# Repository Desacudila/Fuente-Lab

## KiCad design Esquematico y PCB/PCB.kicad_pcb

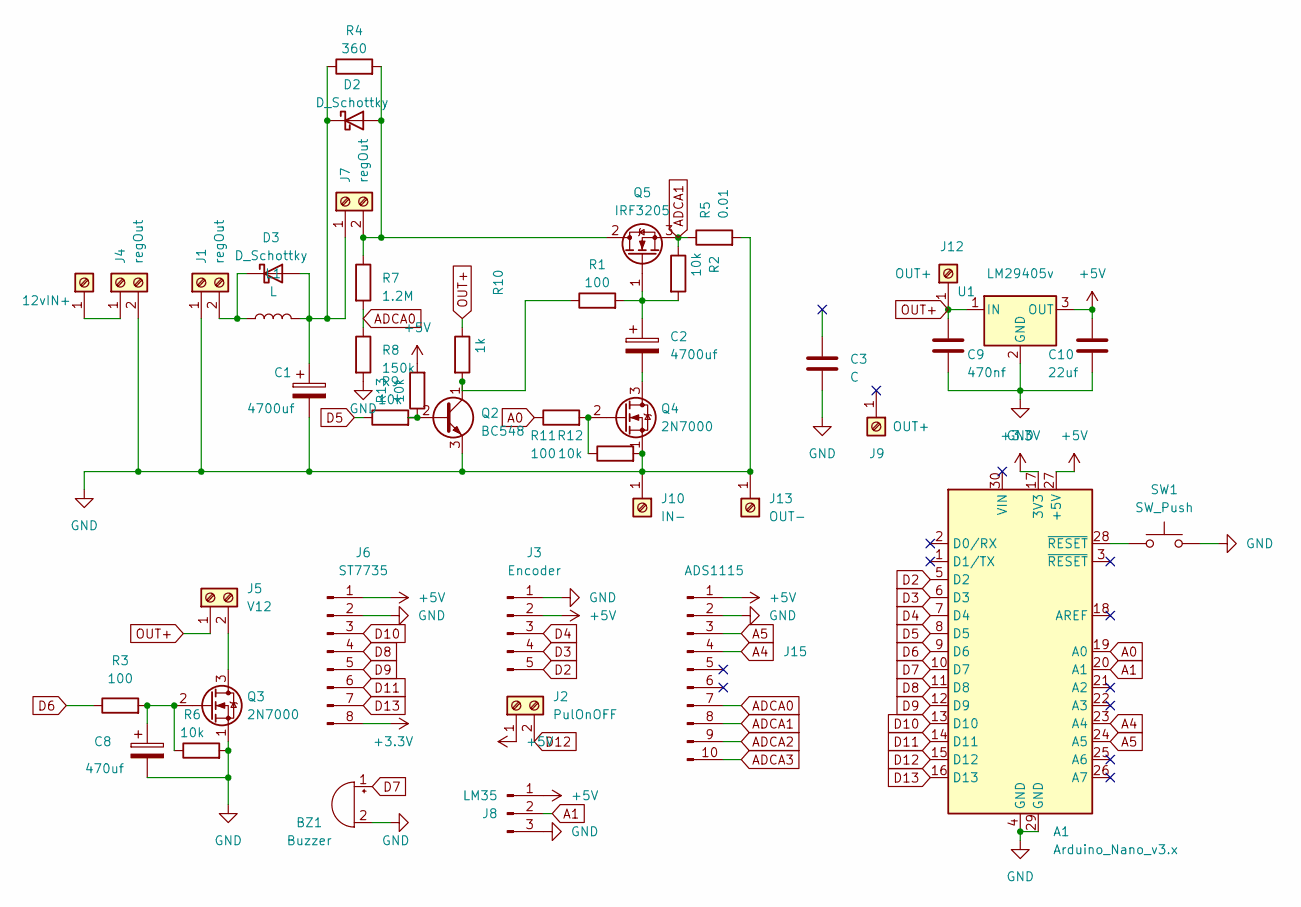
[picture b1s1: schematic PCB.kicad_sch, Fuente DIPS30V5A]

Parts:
A1: Arduino_Nano_v3.x; Arduino_Nano_WithMountingHoles
BZ1: Buzzer; MagneticBuzzer_ProSignal_ABI-010-RC
C1, C2: 4700uf; CP_Radial_D22.0mm_P10.00mm_SnapIn
C3: C; C_Rect_L26.5mm_W7.0mm_P22.50mm_MKS4
C8: 470uf; C_Radial_D10.0mm_H16.0mm_P5.00mm
C9: 470nf; C_Disc_D5.0mm_W2.5mm_P5.00mm
C10: 22uf; CP_Radial_D4.0mm_P2.00mm
D2, D3: D_Schottky; D_DO-201AD_P15.24mm_Horizontal
J1, J4, J7: regOut; Molex_KK-254_AE-6410-02A_1x02_P2.54mm_Vertical
J2: PulOnOFF; Molex_KK-254_AE-6410-02A_1x02_P2.54mm_Vertical
J3: Encoder; Molex_KK-254_AE-6410-05A_1x05_P2.54mm_Vertical
J5: V12; Molex_KK-254_AE-6410-02A_1x02_P2.54mm_Vertical
J6: ST7735; Molex_KK-254_AE-6410-08A_1x08_P2.54mm_Vertical
J8: LM35; Molex_KK-254_AE-6410-03A_1x03_P2.54mm_Vertical
J9, J12: OUT+; Pin_D1.0mm_L10.0mm
J10: IN-; Pin_D1.0mm_L10.0mm
J13: OUT-; Pin_D1.0mm_L10.0mm
J15: ADS1115; PinHeader_1x10_P2.54mm_Vertical
J16: 12vIN+; Pin_D1.0mm_L10.0mm
L1: L; L_Toroid_Vertical_L21.6mm_W8.4mm_P8.38mm_Pulse_G
Q2: BC548; TO-92_Inline
Q3, Q4: 2N7000; TO-92_Inline
Q5: IRF3205; TO-220-3_Vertical
R1, R3, R11: 100; R_Axial_DIN0207_L6.3mm_D2.5mm_P10.16mm_Horizontal
R2, R6, R9, R12, R13: 10k; R_Axial_DIN0207_L6.3mm_D2.5mm_P10.16mm_Horizontal
R4: 360; R_Axial_Power_L38.0mm_W6.4mm_P45.72mm
R5: 0.01; R_2512_6332Metric_Pad1.40x3.35mm_HandSolder
R7: 1.2M; R_Axial_DIN0207_L6.3mm_D2.5mm_P10.16mm_Horizontal
R8: 150k; R_Axial_DIN0207_L6.3mm_D2.5mm_P10.16mm_Horizontal
R10: 1k; R_Axial_DIN0207_L6.3mm_D2.5mm_P10.16mm_Horizontal
SW1: SW_Push; Molex_KK-254_AE-6410-02A_1x02_P2.54mm_Vertical
U1: LM29405v; TO-220-3_Horizontal_TabDown

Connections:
+3.3V: A1.17 (3V3), J6.8
+5V: A1.27 (+5V), C10.1, J2.1, J3.2, J6.1, J8.1, J15.1, R13.2, U1.3 (OUT)
A0: A1.19 (A0), R11.1
A1: A1.20 (A1), J8.2
A4: A1.23 (A4), J15.4
A5: A1.24 (A5), J15.3
ADCA0: J15.7, R7.2, R8.1
ADCA1: J15.8, Q5.3 (S), R2.1, R5.1
ADCA2: J15.9
ADCA3: J15.10
D2: A1.5 (D2), J3.5
D3: A1.6 (D3), J3.4
D4: A1.7 (D4), J3.3
D5: A1.8 (D5), R9.1
D6: A1.9 (D6), R3.1
D7: A1.10 (D7), BZ1.1 (-)
D8: A1.11 (D8), J6.4
D9: A1.12 (D9), J6.5
D10: A1.13 (D10), J6.3
D11: A1.14 (D11), J6.6
D12: A1.15 (D12), J2.2
D13: A1.16 (D13), J6.7
GND: A1.4 (GND), A1.29 (GND), BZ1.2 (+), C1.2, C3.2, C8.2, C9.2, C10.2, J1.1, J3.1, J4.2, J6.2, J8.3, J10.1, J13.1, J15.2, Q2.3 (E), Q3.1 (S), Q4.1 (S), R5.2, R6.2, R8.2, R12.2, SW1.2, U1.2 (GND)
unnamed: A1.28 (~RESET), SW1.1
unnamed: D2.2 (A), J7.2, Q5.2 (D), R4.2, R7.1
unnamed: C1.1, D2.1 (K), D3.2 (A), J7.1, L1.2, R4.1
unnamed: D3.1 (K), J1.2, L1.1
unnamed: J5.2, Q3.3 (D)
unnamed: J4.1, J16.1
unnamed: Q2.2 (B), R9.2, R13.1
unnamed: Q2.1 (C), R1.1, R10.2
unnamed: C8.1, Q3.2 (G), R3.2, R6.1
unnamed: C2.2, Q4.3 (D)
unnamed: Q4.2 (G), R11.2, R12.1
unnamed: C2.1, Q5.1 (G), R1.2, R2.2
OUT+: C9.1, J5.1, J12.1, R10.1, U1.1 (IN)

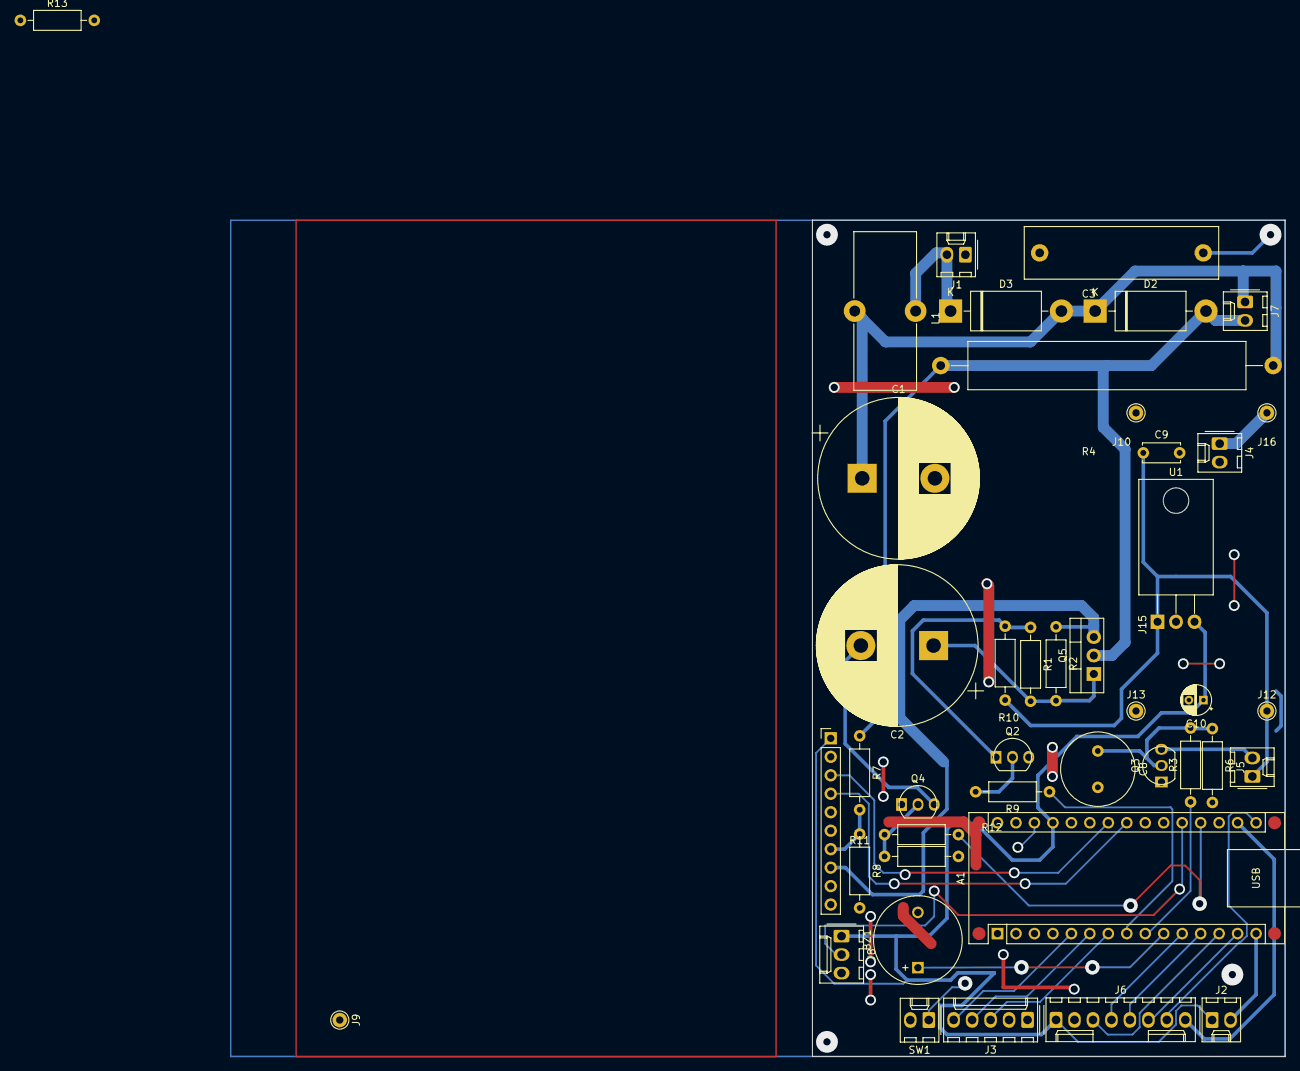
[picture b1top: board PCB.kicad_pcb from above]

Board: 2 copper layers, 65.0 x 115.0 mm, 44 parts (1 on the bottom side), 34 nets.

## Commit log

2023-05-29 nombre
